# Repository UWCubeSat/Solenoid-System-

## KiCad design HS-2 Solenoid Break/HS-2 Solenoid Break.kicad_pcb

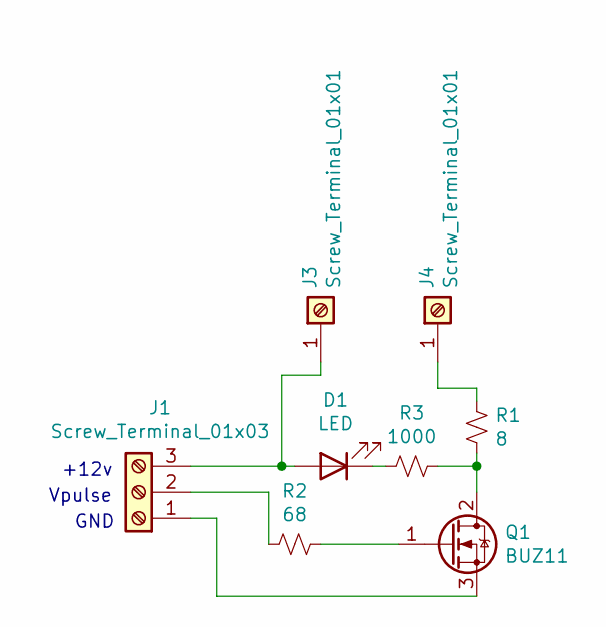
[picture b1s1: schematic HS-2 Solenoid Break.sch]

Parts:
D1: LED; LED_D5.0mm
J1: Screw_Terminal_01x03; PinSocket_1x03_P2.54mm_Vertical
J3, J4: Screw_Terminal_01x01; PinSocket_1x01_P2.54mm_Vertical
Q1: BUZ11; TO-220-3_Vertical
R1: 8; R_Axial_DIN0207_L6.3mm_D2.5mm_P10.16mm_Horizontal
R2: 68; R_Axial_DIN0207_L6.3mm_D2.5mm_P10.16mm_Horizontal
R3: 1000; R_Axial_DIN0207_L6.3mm_D2.5mm_P10.16mm_Horizontal

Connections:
unnamed: D1.1 (K), R3.2
unnamed: D1.2 (A), J1.3, J3.1
unnamed: J1.1, Q1.3 (S)
unnamed: J1.2, R2.2
unnamed: J4.1, R1.2
unnamed: Q1.1 (G), R2.1
unnamed: Q1.2 (D), R1.1, R3.1

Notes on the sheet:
Vpulse
+12v
GND

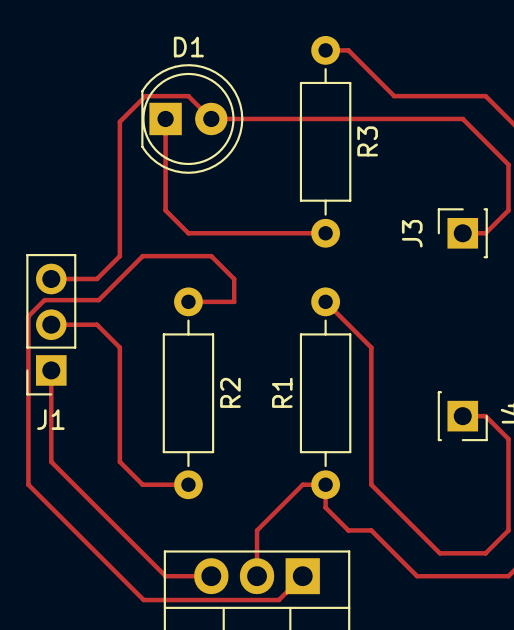
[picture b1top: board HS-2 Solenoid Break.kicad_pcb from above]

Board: 2 copper layers, 8 parts (0 on the bottom side), 7 nets.

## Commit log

2021-02-17 Mounting Holes and Diode
    Added mounting holes for deployable system, and a flyback diode to prevent voltage spike of solenoid.
